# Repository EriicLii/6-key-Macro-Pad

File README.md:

# 6 Key Macro Pad

Footprints from https://github.com/tmk/keyboard_parts.pretty and https://github.com/egladman/keebs.pretty

Components used from https://github.com/tmk/kicad_lib_tmk

Built with SMD components, and ATMega32u4.

PCB:

Schematic:

## Update 7/31
Finally got to soldering the parts. 
Had an issue with discovering the DFU. At first I though the microcontroller didn't come with the HWBE bit set from factory. However after painstakingly soldering the MOSI, MISO and SCK pins, then setting the fuses through ISP -- still no dice. I finally noticed that I hadn't wired VBus to VCC in my schematic. I guess I got taught the lesson of measuring thrice before sending it to fabrication.

QMK firmware setup was very easy. Kudos to everyone involved in the project as the abundance documentation and organization made it simple to get a new keyboard firmware set up. Right now I only have the option to manually change the keymaps in QMK then recompile. I'll perhaps attempt to make a Via keymap later as well. (Also I need to add pictures of the build!)

## Update 8/2
Added some pictures. You can see how I had to wire VCC to the Vbus pin on the back of the board.

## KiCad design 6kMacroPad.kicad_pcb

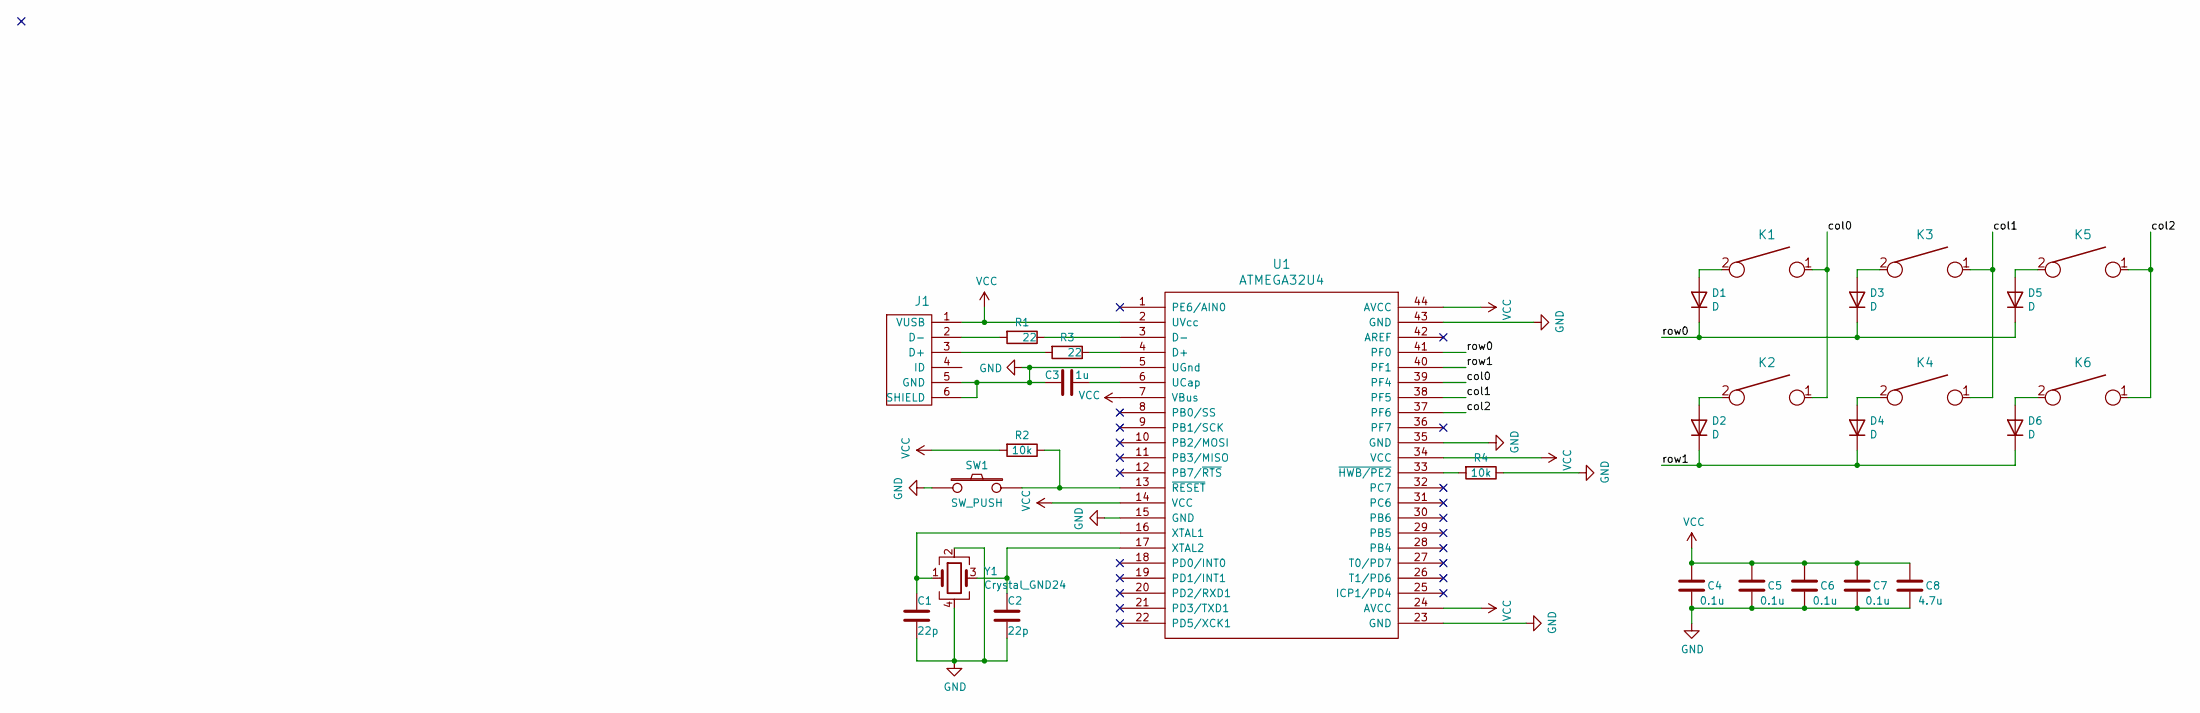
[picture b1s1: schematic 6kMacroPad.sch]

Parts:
C1, C2: 22p; C_0805_2012Metric_Pad1.15x1.40mm_HandSolder
C3: 1u; C_0805_2012Metric_Pad1.15x1.40mm_HandSolder
C4, C5, C6, C7: 0.1u; C_0805_2012Metric_Pad1.15x1.40mm_HandSolder
C8: 4.7u; C_0805_2012Metric_Pad1.15x1.40mm_HandSolder
D1, D2, D3, D4, D5, D6: D; D_SOD123_axial
J1: USB_mini_micro_B; USB_miniB_hirose_5S8
K1, K2, K3, K4, K5, K6: KEYSW; Mx_Alps_100
R1, R3: 22; R_0805_2012Metric_Pad1.15x1.40mm_HandSolder
R2, R4: 10k; R_0805_2012Metric_Pad1.15x1.40mm_HandSolder
SW1: SW_PUSH; SW_SPST_TL3342
U1: ATMEGA32U4; TQFP-44_10x10mm_P0.8mm
Y1: Crystal_GND24; Crystal_SMD_SeikoEpson_FA238-4Pin_3.2x2.5mm_HandSoldering

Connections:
/col0: K1.1, K2.1, U1.39 (PF4)
/col1: K3.1, K4.1, U1.38 (PF5)
/col2: K5.1, K6.1, U1.37 (PF6)
/row0: D1.1 (K), D3.1 (K), D5.1 (K), U1.41 (PF0)
/row1: D2.1 (K), D4.1 (K), D6.1 (K), U1.40 (PF1)
GND: C1.2, C2.2, C3.2, C4.2, C5.2, C6.2, C7.2, C8.2, J1.5 (GND), J1.6 (SHIELD), R4.1, SW1.1, U1.5 (UGnd), U1.15 (GND), U1.23 (GND), U1.35 (GND), U1.43 (GND), Y1.2, Y1.4
unnamed: C1.1, U1.16 (XTAL1), Y1.1
unnamed: C2.1, U1.17 (XTAL2), Y1.3
unnamed: C3.1, U1.6 (UCap)
unnamed: D1.2 (A), K1.2
unnamed: D2.2 (A), K2.2
unnamed: D3.2 (A), K3.2
unnamed: D4.2 (A), K4.2
unnamed: D5.2 (A), K5.2
unnamed: D6.2 (A), K6.2
unnamed: J1.2 (D-), R1.2
unnamed: J1.3 (D+), R3.2
unnamed: R1.1, U1.3 (D-)
unnamed: R2.1, SW1.2, U1.13 (~RESET)
unnamed: R3.1, U1.4 (D+)
unnamed: R4.2, U1.33 (~HWB/PE2)
VCC: C4.1, C5.1, C6.1, C7.1, C8.1, J1.1 (VUSB), R2.2, U1.2 (UVcc), U1.7 (VBus), U1.14 (VCC), U1.24 (AVCC), U1.34 (VCC), U1.44 (AVCC)

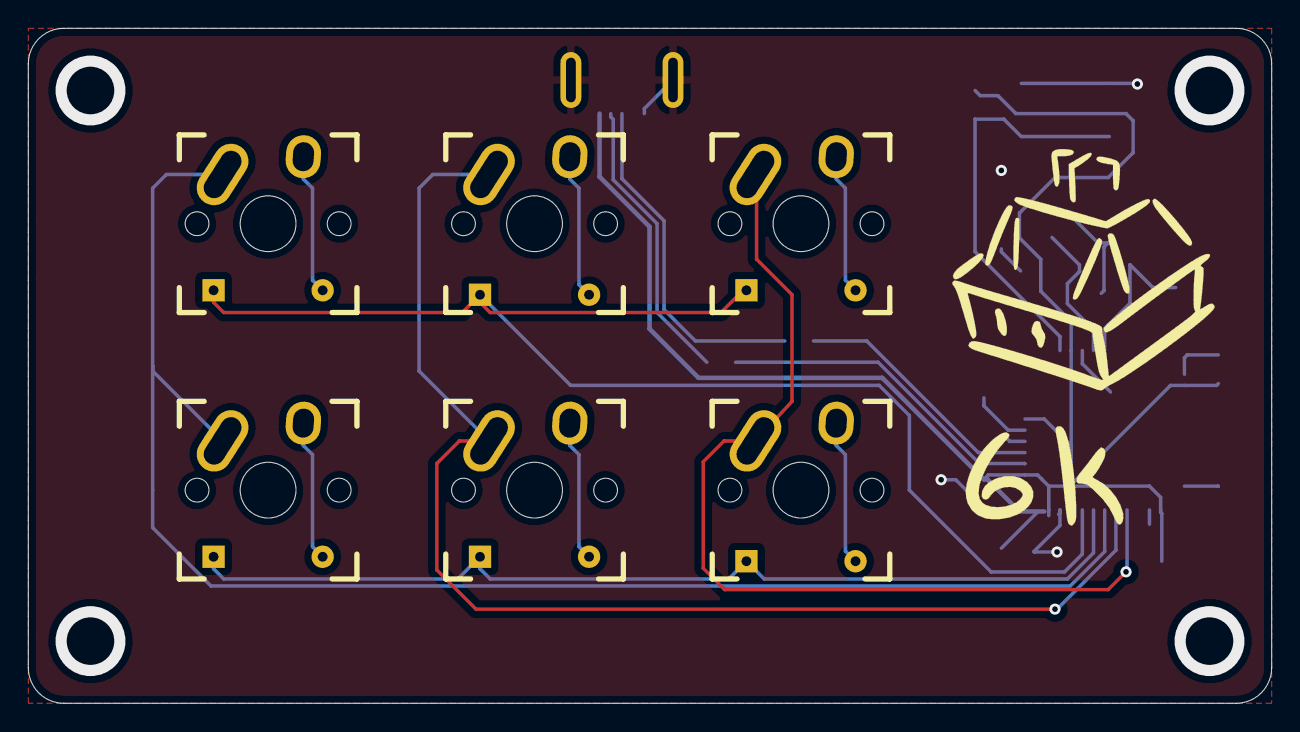
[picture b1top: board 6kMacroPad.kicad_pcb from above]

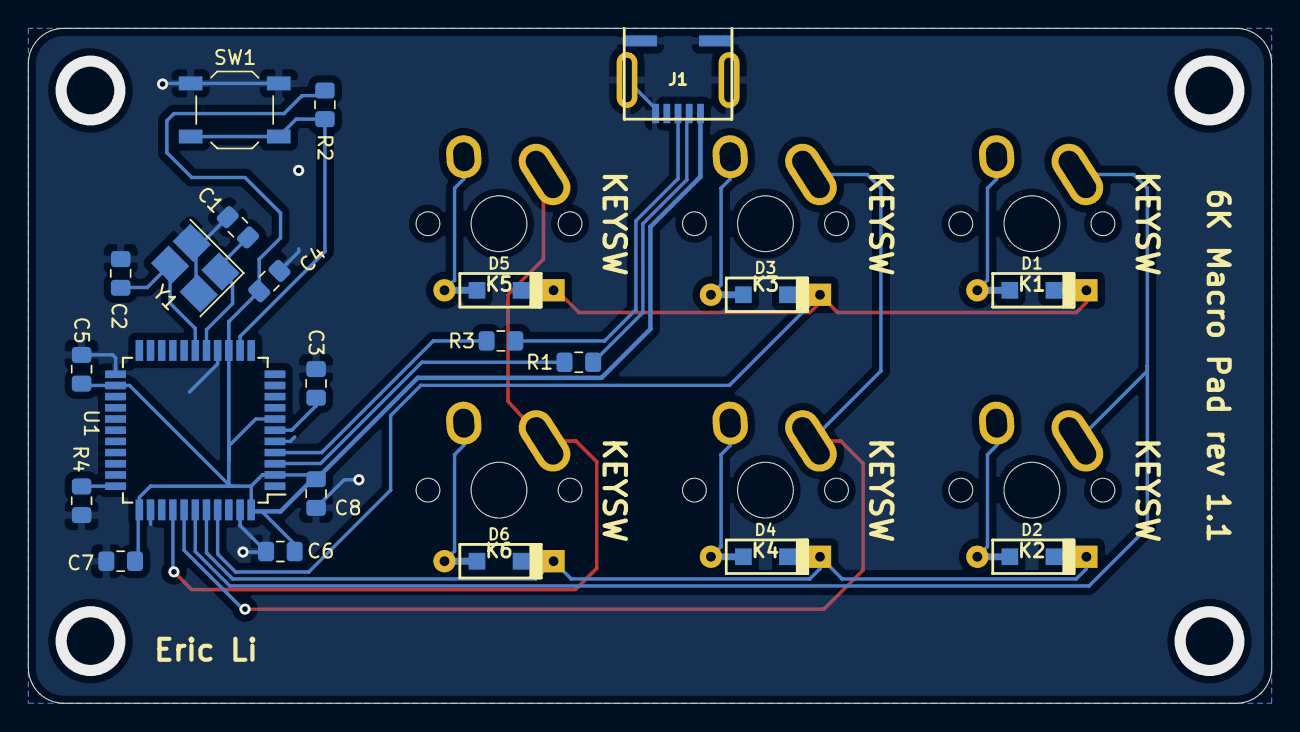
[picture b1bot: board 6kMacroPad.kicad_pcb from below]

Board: 2 copper layers, 88.9 x 48.3 mm, 28 parts (22 on the bottom side), 22 nets.

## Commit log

2020-07-31 Added pngs, and project file
2020-07-31 Update README with images
2020-08-01 Update Readme.md
    Build update
2020-08-02 Fixed Vbus not connected, added pics
    - now Vbus is connected to VCC
    - added more pics of the build
2020-08-02 Added images to README
2020-08-02 Fixed PCB and Schematic links in README
